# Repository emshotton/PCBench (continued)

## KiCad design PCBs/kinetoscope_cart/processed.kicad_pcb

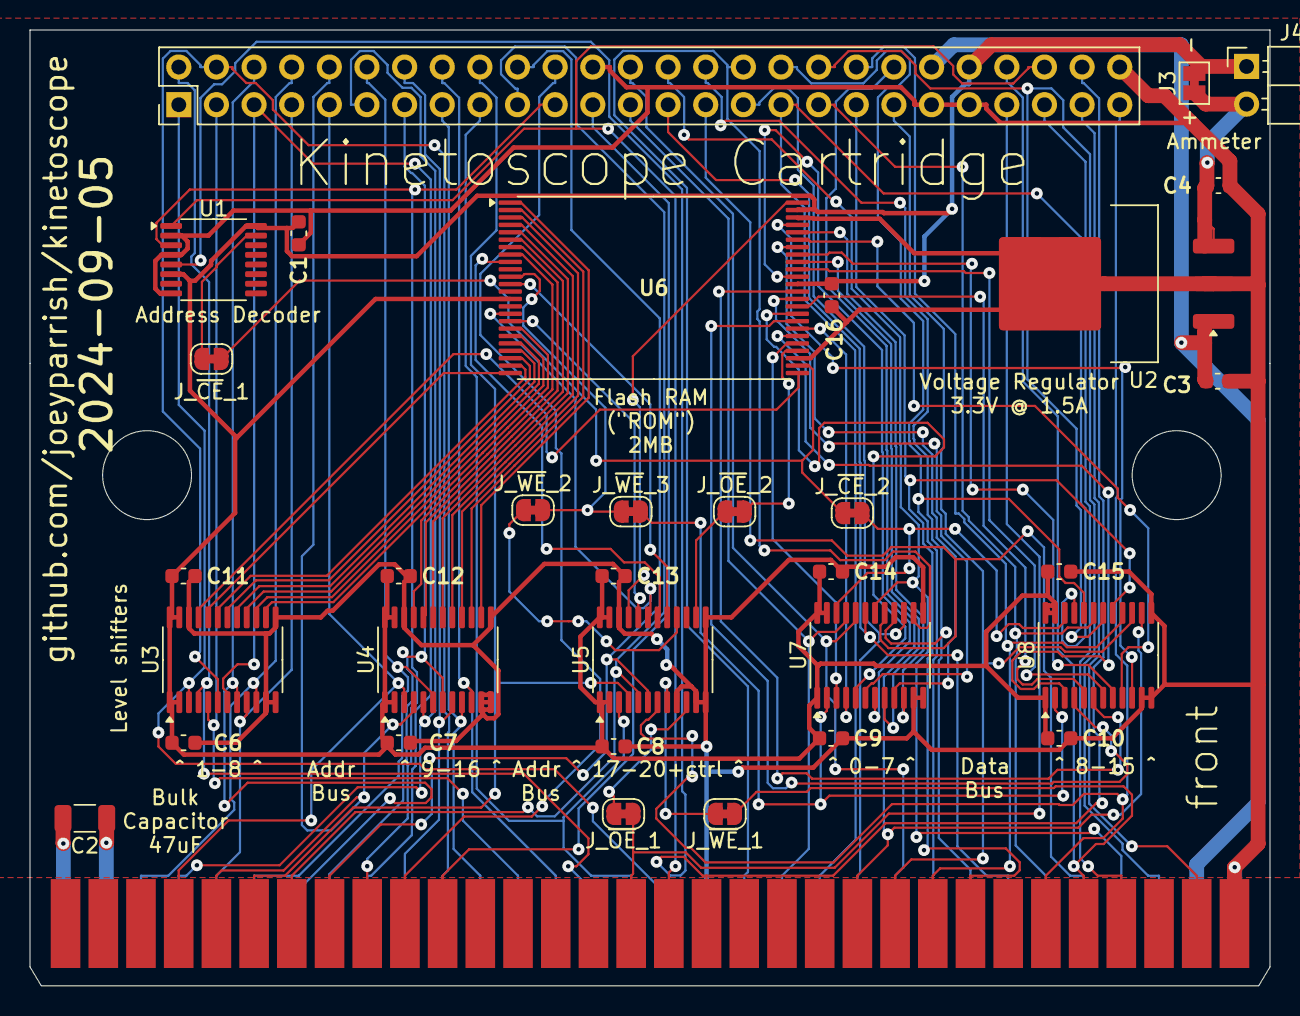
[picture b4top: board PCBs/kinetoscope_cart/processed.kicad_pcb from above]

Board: 2 copper layers, 83.7 x 64.5 mm, 34 parts (0 on the bottom side), 99 nets.

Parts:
C1, C6, C7, C8, C9, C10, C11, C12, C13, C14, C15, C16: 22nF; C_0603_1608Metric
C2: 47uF; C_1206_3216Metric
C3: 4.7uF; C_0603_1608Metric
C4: 1uF; C_0603_1608Metric
J1: PinHeader_2x26_P2.54mm_Vertical
J3: SolderJumper-2_P1.3mm_Bridged_Pad1.0x1.5mm
J4: debug-snoop; PinHeader_1x02_P2.54mm_Horizontal
J_~{CE}_1, J_~{CE}_2: SolderJumper-2_P1.3mm_Bridged_RoundedPad1.0x1.5mm
J_~{OE}_1, J_~{OE}_2: SolderJumper-2_P1.3mm_Bridged_RoundedPad1.0x1.5mm
J_~{WE}_1, J_~{WE}_2, J_~{WE}_3: SolderJumper-2_P1.3mm_Bridged_RoundedPad1.0x1.5mm
P1: edge connector; MD-CART-FINGERS
U1: 74LVC138A; TSSOP-16_4.4x5mm_P0.65mm
U2: MCP1827S-3302E/EB; TO-252-3_TabPin2
U3, U4, U5, U7, U8: 74LVC8T245; TSSOP-24_4.4x7.8mm_P0.65mm
U6: S29AL016J55TFIR20; TSOP-I-48_18.4x12mm_P0.5mm

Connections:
+3.3V: C1.1, C6.1, C7.1, C8.1, C9.1, C10.1, C11.1, C12.1, C13.1, C14.1, C15.1, C16.1, J1.44 (3V), J3.2 (B), J4.1, U1.6 (E2), U1.16 (VCC), U3.1 (V_{CCA}), U3.2 (DIR), U3.23 (V_{CCB}), U3.24 (V_{CCB}), U4.1 (V_{CCA}), U4.2 (DIR), U4.23 (V_{CCB}), U4.24 (V_{CCB}), U5.1 (V_{CCA}), U5.2 (DIR), U5.23 (V_{CCB}), U5.24 (V_{CCB}), U6.14 (~WP), U6.37 (VCC), U6.47 (~BYTE), U7.1 (V_{CCA}), U7.23 (V_{CCB}), U7.24 (V_{CCB}), U8.1 (V_{CCA}), U8.23 (V_{CCB}), U8.24 (V_{CCB})
+5V: C3.1, J1.42 (5V), P1.A31 (+5V), U2.1 (VI)
+5VP: C2.1, P1.A2 (+5V)
/+3.3V_INT: C4.1, J3.1 (A), J4.2, U2.3 (VO)
/SEGA_A1: J1.1 (SEGA_A1), P1.A17 (A1), U3.3 (A1)
/SEGA_A2: J1.2 (SEGA_A2), P1.A15 (A2), U3.4 (A2)
/SEGA_A3: J1.3 (SEGA_A3), P1.A13 (A3), U3.5 (A3)
/SEGA_A4: J1.4 (SEGA_A4), P1.A11 (A4), U3.6 (A4)
/SEGA_A5: J1.5 (SEGA_A5), P1.A9 (A5), U3.7 (A5)
/SEGA_A6: J1.6 (SEGA_A6), P1.A7 (A6), U3.8 (A6)
/SEGA_A7: J1.7 (SEGA_A7), P1.A5 (A7), U3.9 (A7)
/SEGA_A8: J1.8 (SEGA_A8), P1.A3 (A8), U3.10 (A8)
/SEGA_A9: J1.9 (SEGA_A9), P1.B4 (A9), U4.3 (A1)
/SEGA_A10: J1.10 (SEGA_A10), P1.B5 (A10), U4.4 (A2)
/SEGA_A11: J1.11 (SEGA_A11), P1.A4 (A11), U4.5 (A3)
/SEGA_A12: J1.12 (SEGA_A12), P1.A6 (A12), U4.6 (A4)
/SEGA_A13: J1.13 (SEGA_A13), P1.A8 (A13), U4.7 (A5)
/SEGA_A14: J1.14 (SEGA_A14), P1.A10 (A14), U4.8 (A6)
/SEGA_A15: J1.15 (SEGA_A15), P1.A12 (A15), U4.9 (A7)
/SEGA_A16: J1.16 (SEGA_A16), P1.A14 (A16), U4.10 (A8)
/SEGA_A17: J1.17 (SEGA_A17), P1.A16 (A17), U5.3 (A1)
/SEGA_A18: J1.18 (SEGA_A18), P1.B6 (A18), U5.4 (A2)
/SEGA_A19: J1.19 (SEGA_A19), P1.B7 (A19), U5.5 (A3)
/SEGA_A20: J1.20 (SEGA_A20), P1.B8 (A20), U5.6 (A4)
/SEGA_A21: J1.21 (SEGA_A21), P1.B9 (A21), U1.3 (A2)
/SEGA_A22: J1.22 (SEGA_A22), P1.B10 (A22)
/SEGA_A23: J1.23 (SEGA_A23), P1.B11 (A23)
/SEGA_D0: J1.25 (SEGA_D0), P1.A20 (D0), U7.21 (B1)
/SEGA_D1: J1.26 (SEGA_D1), P1.A23 (D1), U7.20 (B2)
/SEGA_D2: J1.27 (SEGA_D2), P1.A26 (D2), U7.19 (B3)
/SEGA_D3: J1.28 (SEGA_D3), P1.A29 (D3), U7.18 (B4)
/SEGA_D4: J1.29 (SEGA_D4), P1.A28 (D4), U7.17 (B5)
/SEGA_D5: J1.30 (SEGA_D5), P1.A25 (D5), U7.16 (B6)
/SEGA_D6: J1.31 (SEGA_D6), P1.A22 (D6), U7.15 (B7)
/SEGA_D7: J1.32 (SEGA_D7), P1.A19 (D7), U7.14 (B8)
/SEGA_D8: J1.33 (SEGA_D8), P1.A21 (D8), U8.21 (B1)
/SEGA_D9: J1.34 (SEGA_D9), P1.A24 (D9), U8.20 (B2)
/SEGA_D10: J1.35 (SEGA_D10), P1.A27 (D10), U8.19 (B3)
/SEGA_D11: J1.36 (SEGA_D11), P1.A30 (D11), U8.18 (B4)
/SEGA_D12: J1.37 (SEGA_D12), P1.B25 (D12), U8.17 (B5)
/SEGA_D13: J1.38 (SEGA_D13), P1.B24 (D13), U8.16 (B6)
/SEGA_D14: J1.39 (SEGA_D14), P1.B23 (D14), U8.15 (B7)
/SEGA_D15: J1.40 (SEGA_D15), P1.B22 (D15), U8.14 (B8)
/flash-internal/A0_3V: U3.21 (B1), U6.25 (A0)
/flash-internal/A1_3V: U3.20 (B2), U6.24 (A1)
/flash-internal/A2_3V: U3.19 (B3), U6.23 (A2)
/flash-internal/A3_3V: U3.18 (B4), U6.22 (A3)
/flash-internal/A4_3V: U3.17 (B5), U6.21 (A4)
/flash-internal/A5_3V: U3.16 (B6), U6.20 (A5)
/flash-internal/A6_3V: U3.15 (B7), U6.19 (A6)
/flash-internal/A7_3V: U3.14 (B8), U6.18 (A7)
/flash-internal/A8_3V: U4.21 (B1), U6.8 (A8)
/flash-internal/A9_3V: U4.20 (B2), U6.7 (A9)
/flash-internal/A10_3V: U4.19 (B3), U6.6 (A10)
/flash-internal/A11_3V: U4.18 (B4), U6.5 (A11)
/flash-internal/A12_3V: U4.17 (B5), U6.4 (A12)
/flash-internal/A13_3V: U4.16 (B6), U6.3 (A13)
/flash-internal/A14_3V: U4.15 (B7), U6.2 (A14)
/flash-internal/A15_3V: U4.14 (B8), U6.1 (A15)
/flash-internal/A16_3V: U5.21 (B1), U6.48 (A16)
/flash-internal/A17_3V: U5.20 (B2), U6.17 (A17)
/flash-internal/A18_3V: U5.19 (B3), U6.16 (A18)
/flash-internal/A19_3V: U5.18 (B4), U6.9 (A19)
/flash-internal/D0_3V: U6.29 (DQ0), U7.3 (A1)
/flash-internal/D1_3V: U6.31 (DQ1), U7.4 (A2)
/flash-internal/D2_3V: U6.33 (DQ2), U7.5 (A3)
/flash-internal/D3_3V: U6.35 (DQ3), U7.6 (A4)
/flash-internal/D4_3V: U6.38 (DQ4), U7.7 (A5)
/flash-internal/D5_3V: U6.40 (DQ5), U7.8 (A6)
/flash-internal/D6_3V: U6.42 (DQ6), U7.9 (A7)
/flash-internal/D7_3V: U6.44 (DQ7), U7.10 (A8)
/flash-internal/D8_3V: U6.30 (DQ8), U8.3 (A1)
/flash-internal/D9_3V: U6.32 (DQ9), U8.4 (A2)
/flash-internal/D10_3V: U6.34 (DQ10), U8.5 (A3)
/flash-internal/D11_3V: U6.36 (DQ11), U8.6 (A4)
/flash-internal/D12_3V: U6.39 (DQ12), U8.7 (A5)
/flash-internal/D13_3V: U6.41 (DQ13), U8.8 (A6)
/flash-internal/D14_3V: U6.43 (DQ14), U8.9 (A7)
/flash-internal/D15_3V: U6.45 (DQ15/A-1), U8.10 (A8)
/flash-internal/DATA_DIR_INT: J_~{WE}_3.2 (B), U7.2 (DIR), U8.2 (DIR)
/flash-internal/~CE_3V_INT: J_~{CE}_1.2 (B), J_~{CE}_2.1 (A), U6.26 (~CE)
/flash-internal/~DATA_OE_INT: J_~{CE}_2.2 (B), U7.22 (~OE), U8.22 (~OE)
/flash-internal/~OE_3V_INT: J_~{OE}_2.2 (B), U6.28 (~OE)
/flash-internal/~OE_3V: J_~{OE}_2.1 (A), U5.14 (B8)
/flash-internal/~OE_INT: J_~{OE}_1.2 (B), U5.10 (A8)
/flash-internal/~RESET_3V: U5.17 (B5), U6.12 (~RESET)
/flash-internal/~WE_3V_INT: J_~{WE}_2.2 (B), J_~{WE}_3.1 (A), U6.11 (~WE)
/flash-internal/~WE_3V: J_~{WE}_2.1 (A), U5.16 (B6)
/flash-internal/~WE_INT: J_~{WE}_1.2 (B), U5.8 (A6)
/~FLASH_CE: J_~{CE}_1.1 (A), U1.15 (~Y0)
/~SEGA_AS: J1.50 (~SEGA_AS), P1.B18 (~AS), U1.5 (~E1)
/~SEGA_CE: J1.48 (~SEGA_CE), P1.B17 (~C_CE), U1.1 (A0)
/~SEGA_OE: J1.45 (~SEGA_OE), J_~{OE}_1.1 (A), P1.B16 (~C_OE)
/~SEGA_REGISTER: J1.49 (~SEGA_REGISTER), P1.B31 (~TIME)
/~SEGA_RESET: J1.51 (~SEGA_RESET), P1.B27 (~RESET), U5.7 (A5)
/~SEGA_WE_LB: J1.46 (~SEGA_WE_LB), J_~{WE}_1.1 (A), P1.B28 (~LDSW)
/~SEGA_WE_UB: J1.47 (~SEGA_WE_UB), P1.B29 (~UDSW)
GND: C1.2, C3.2, C4.2, C6.2, C7.2, C8.2, C9.2, C10.2, C11.2, C12.2, C13.2, C14.2, C15.2, C16.2, J1.24 (GND), J1.41 (GND), J1.43 (GND), J1.52 (GND), P1.A18 (GND), P1.A32 (GND), P1.B32 (~CART_IN), U1.2 (A1), U1.4 (~E0), U1.8 (GND), U2.2 (ADJ), U3.11 (GND), U3.12 (GND), U3.13 (GND), U3.22 (~OE), U4.11 (GND), U4.12 (GND), U4.13 (GND), U4.22 (~OE), U5.9 (A7), U5.11 (GND), U5.12 (GND), U5.13 (GND), U5.22 (~OE), U6.27 (VSS1), U6.46 (VSS2), U7.11 (GND), U7.12 (GND), U7.13 (GND), U8.11 (GND), U8.12 (GND), U8.13 (GND)
GNDPWR: C2.2, P1.A1 (GND)
